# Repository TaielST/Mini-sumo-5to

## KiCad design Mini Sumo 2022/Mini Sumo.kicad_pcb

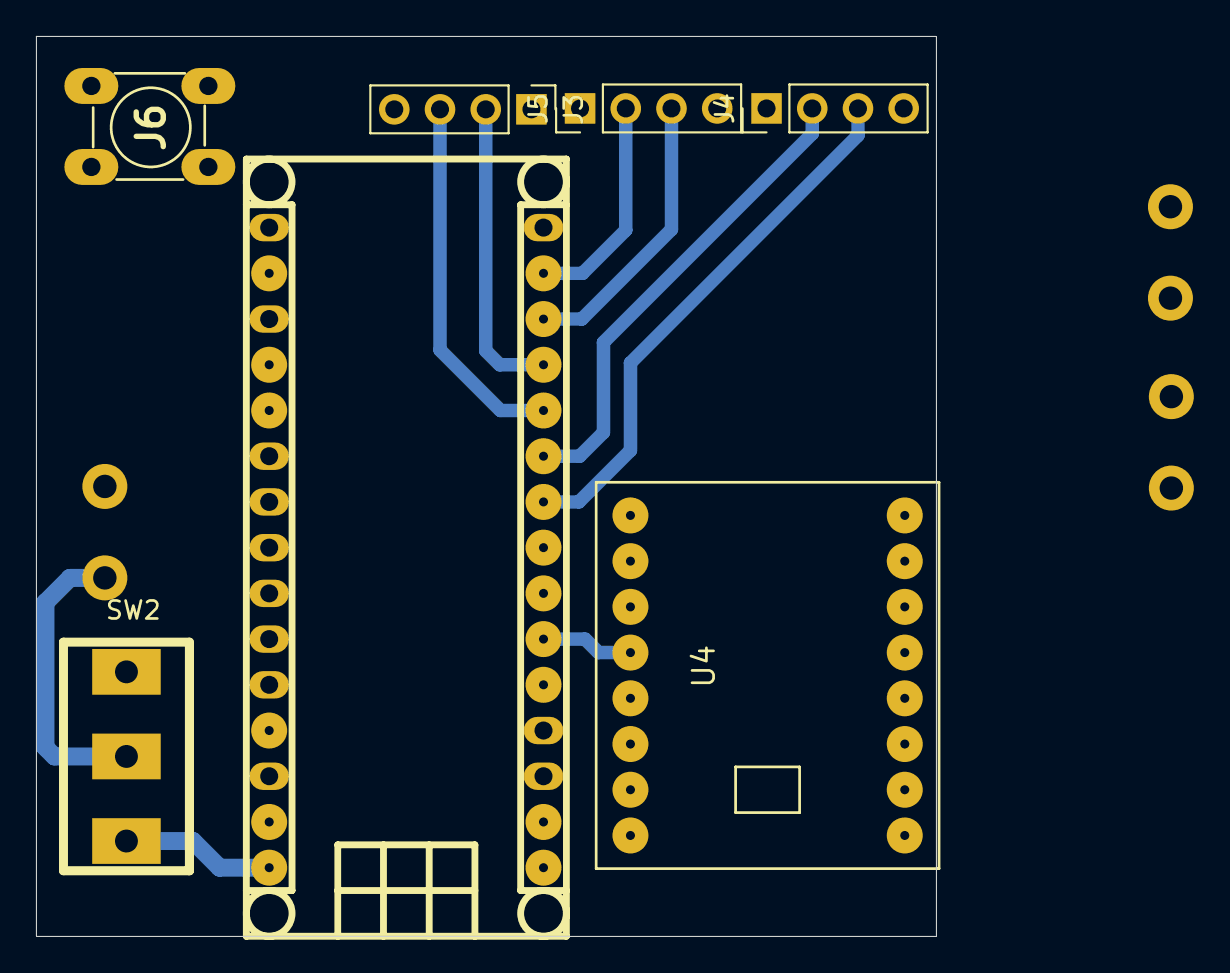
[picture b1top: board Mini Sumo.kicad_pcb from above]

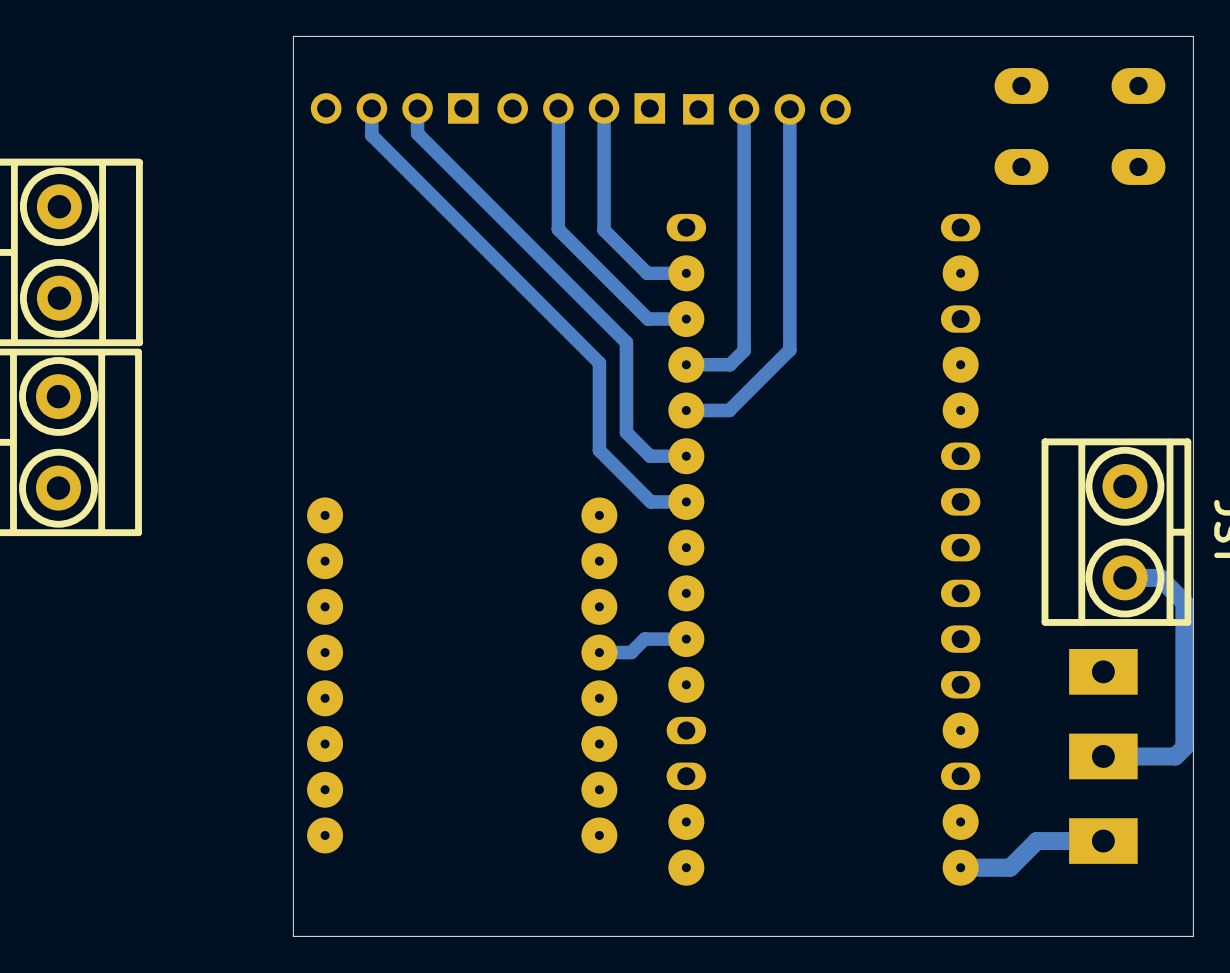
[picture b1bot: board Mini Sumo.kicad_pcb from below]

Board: 2 copper layers, 50.0 x 50.0 mm, 10 parts (3 on the bottom side), 19 nets.

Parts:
Conector1: JST; BORNERA2_AZUL
J1: Arduino_Nano_Header; arduino_nano_header
J3, J4, J5: HC-SR04; PinHeader_1x04_P2.54mm_Vertical
J6: Pulsador; Pulsador_TH_4
Motor1, Motor2: N20; BORNERA2_AZUL
SW2: SW_SPDT; SW_SPDT_TH_Vertical
U4: TB6612_BREAKOUT; TB6612_Breakout

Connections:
+5V: J1.27 (5V), J3.1, J4.1, J5.1, U4.2 (VCC), U4.10 (PWMB), U4.16 (PWMA)
/A5: J1.24 (A5), J6.1
/OUT1: Motor1.2, U4.7 (B1)
/OUT2: Motor1.1, U4.6 (B2)
/OUT3: Motor2.2, U4.5 (A2)
/OUT4: Motor2.1, U4.4 (A1)
/PIN2: J1.8 (D5/T1), U4.11 (BIN2)
/PIN3: J1.6 (D3/INT1), U4.12 (BIN1)
/PIN4: J1.7 (D4/T0), U4.14 (AIN1)
/PIN5: J1.5 (D2/INT0), U4.15 (AIN2)
/PIN6: J1.9 (D6/AIN0), J4.3
/PIN7: J1.10 (D7/AIN1), J4.2
/PIN8: J1.11 (D8/ICP), J3.3
/PIN9: J1.12 (D9/0C1), J3.2
/PIN10: J1.13 (D10/SS), J5.3
/PIN11: J1.14 (D11/MOSI), J5.2
/VCC 1: J1.30 (VIN), SW2.3 (C), U4.1 (VM)
GND: Conector1.2, J1.4 (GND), J1.29 (GND), J3.4, J4.4, J5.4, J6.4, U4.3 (GND), U4.8 (GND), U4.9 (GND)
VCC: Conector1.1, SW2.2 (B)
